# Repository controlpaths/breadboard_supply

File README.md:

# Breadboard Power supply

This tiny board generates all the voltages needed for your signal processing designs. 

This board features a bipolar power supply and a single voltage power supply for control.

The bipolar power supply is managed by a [TPS65131](https://www.ti.com/product/es-mx/TPS65131). A split-rail converter with a maximum output current of 750 mA. The outputs of this power supply is configured for -12 V and +13 volts. 

The board also has a 3v3 volts, 1 Amp output generated by an NCP1529.

All the power rails as well as the the enable input and the input voltage are connected through a 2.54mm right angle connector ready to be inserted into a breadboard. 

## Galery

## Get yours

This board is open-source, so if you want to get yours, you can use the [output_files](./kicad/output_files/) to manufacture your own in [JLCPCB](https://jlcpcb.com/?from=controlpath). You just need to compress the file of the [output_files](./kicad/output_files/) and upload it to [JLCPCB](https://jlcpcb.com/?from=controlpath)

Remember to change the Surface Finish to LeadFree HASL to make your board ROHS compliant.

Also, they can assemble your board using the [centroid](./kicad/output_files/ohe_power_supply_1-all-pos.csv) file and the [BOM](./kicad/output_files/bom.csv) file, which are also available in this repository. Doing this, in a few days you will receive in your home some of these boards.

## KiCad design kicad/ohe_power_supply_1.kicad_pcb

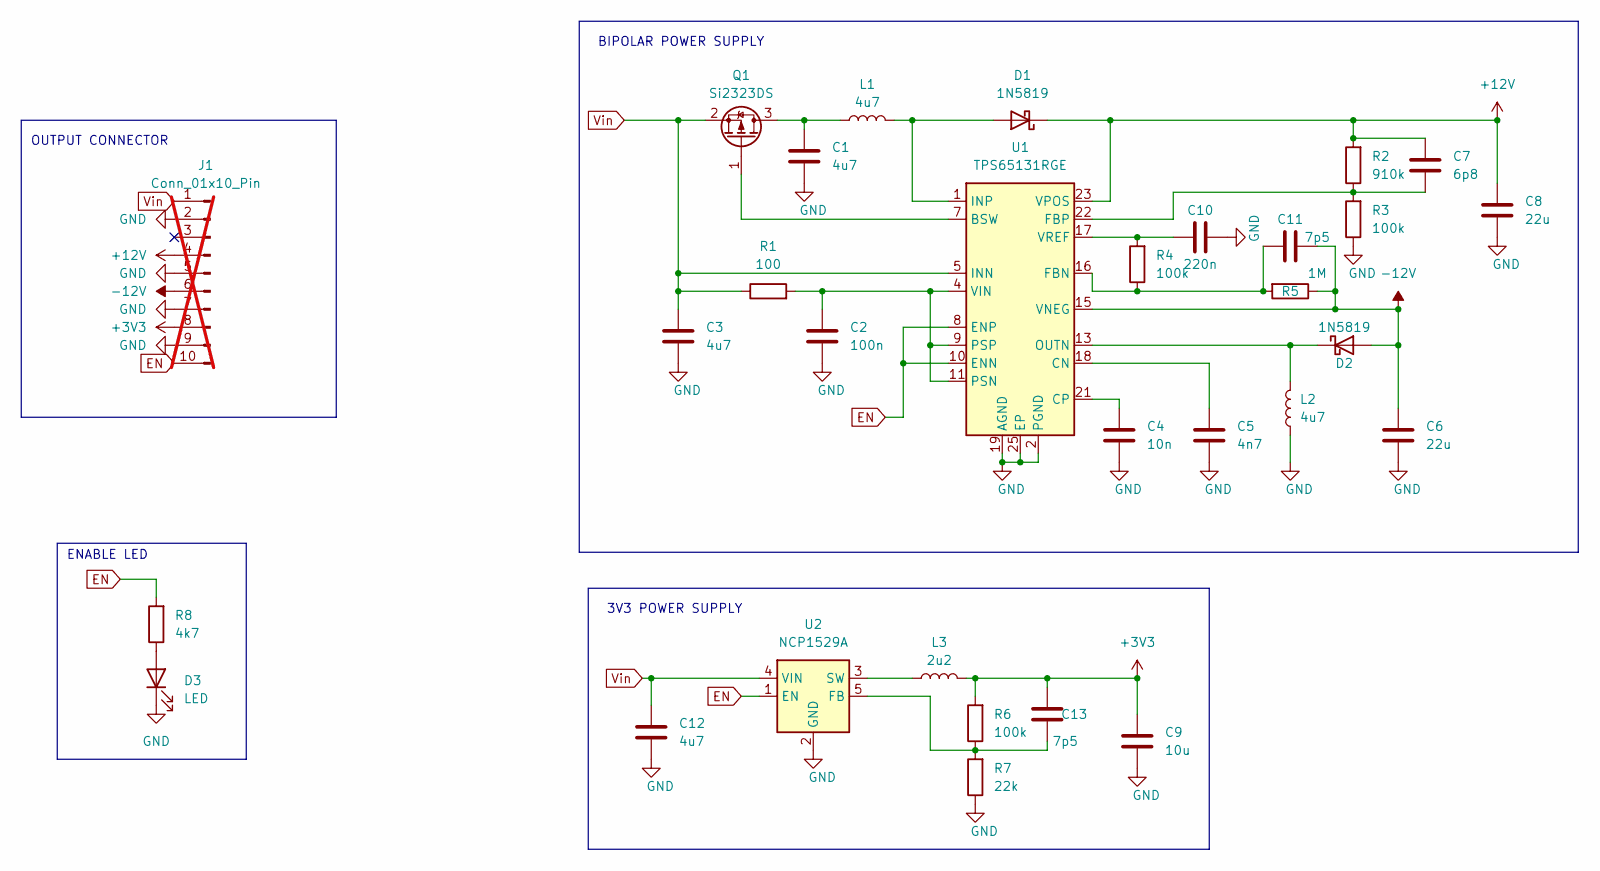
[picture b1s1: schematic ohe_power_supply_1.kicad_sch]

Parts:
C1, C3, C12: 4u7; C_0805_2012Metric
C2: 100n; C_0603_1608Metric
C4: 10n; C_0603_1608Metric
C5: 4n7; C_0603_1608Metric
C6, C8: 22u; C_0805_2012Metric
C7: 6p8; C_0603_1608Metric
C9: 10u; C_0805_2012Metric; JLCPCB Part # C307523
C10: 220n; C_0603_1608Metric
C11, C13: 7p5; C_0603_1608Metric
D1, D2: 1N5819; D_SOD-123; JLCPCB Part # C82544
D3: LED; LED_0603_1608Metric
J1: Conn_01x10_Pin; PinHeader_1x10_P2.54mm_Horizontal; not fitted
L1, L2: 4u7; L_Wurth_WE-LQSH-4020; JLCPCB Part # C2649331
L3: 2u2; L_1008_2520Metric; JLCPCB Part # C668447
Q1: Si2323DS; SOT-23; JLCPCB Part # C165449
R1: 100; R_0603_1608Metric
R2: 910k; R_0805_2012Metric; JLCPCB Part # C425483
R3, R4, R6: 100k; R_0603_1608Metric
R5: 1M; R_0603_1608Metric
R7: 22k; R_0603_1608Metric
R8: 4k7; R_0603_1608Metric
U1: TPS65131RGE; VQFN-24-1EP_4x4mm_P0.5mm_EP2.45x2.45mm_ThermalVias; JLCPCB Part # C87663
U2: NCP1529A; SOT-23-5

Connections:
+3V3: C9.1, C13.1, J1.8, L3.2, R6.2
+12V: C7.1, C8.1, D1.1 (K), J1.4, R2.2, U1.23 (VPOS)
-12V: C6.1, C11.2, D2.2 (A), J1.6, R5.1, U1.15 (VNEG)
EN: J1.10, R8.2, U1.8 (ENP), U1.10 (ENN), U2.1 (EN)
GND: C1.2, C2.2, C3.2, C4.2, C5.2, C6.2, C8.2, C9.2, C10.2, C12.2, D3.1 (K), J1.2, J1.5, J1.7, J1.9, L2.1, R3.1, R7.1, U1.2 (PGND), U1.3 (PGND), U1.19 (AGND), U1.25 (EP), U2.2 (GND)
unnamed: D1.2 (A), L1.2, U1.1 (INP), U1.24 (INP)
unnamed: D2.1 (K), L2.2, U1.13 (OUTN), U1.14 (OUTN)
unnamed: D3.2 (A), R8.1
unnamed: C1.1, L1.1, Q1.3 (D)
unnamed: Q1.1 (G), U1.7 (BSW)
unnamed: C5.1, U1.18 (CN)
unnamed: C4.1, U1.21 (CP)
unnamed: C11.1, R4.1, R5.2, U1.16 (FBN)
unnamed: C7.2, R2.1, R3.2, U1.22 (FBP)
unnamed: C2.1, R1.2, U1.4 (VIN), U1.9 (PSP), U1.11 (PSN)
unnamed: C10.1, R4.2, U1.17 (VREF)
unnamed: C13.2, R6.1, R7.2, U2.5 (FB)
unnamed: L3.1, U2.3 (SW)
Vin: C3.1, C12.1, J1.1, Q1.2 (S), R1.1, U1.5 (INN), U1.6 (INN), U2.4 (VIN)

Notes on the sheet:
3V3 POWER SUPPLY
ENABLE LED
OUTPUT CONNECTOR
BIPOLAR POWER SUPPLY

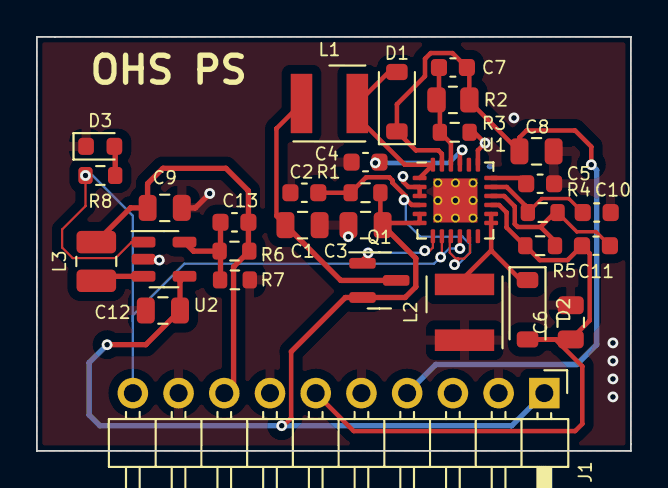
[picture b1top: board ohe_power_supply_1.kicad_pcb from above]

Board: 2 copper layers, 33.0 x 23.0 mm, 31 parts (0 on the bottom side), 19 nets.

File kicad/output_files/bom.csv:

"#","Reference","Qty","Value","Footprint","DNP","JLCPCB Part #"
"1","C1, C3, C12","3","4u7","Capacitor_SMD:C_0805_2012Metric","",""
"2","C2","1","100n","Capacitor_SMD:C_0603_1608Metric","",""
"3","C4","1","10n","Capacitor_SMD:C_0603_1608Metric","",""
"4","C5","1","4n7","Capacitor_SMD:C_0603_1608Metric","",""
"5","C6, C8","2","22u","Capacitor_SMD:C_0805_2012Metric","",""
"6","C7","1","6p8","Capacitor_SMD:C_0603_1608Metric","",""
"7","C9","1","10u","Capacitor_SMD:C_0805_2012Metric","",""
"8","C10","1","220n","Capacitor_SMD:C_0603_1608Metric","",""
"9","C11, C13","2","7p5","Capacitor_SMD:C_0603_1608Metric","",""
"10","D1, D2","2","1N5819","Diode_SMD:D_SOD-123","","C82544"
"11","D3","1","LED","LED_SMD:LED_0603_1608Metric","",""
"12","J1","1","Conn_01x10_Pin","Connector_PinHeader_2.54mm:PinHeader_1x10_P2.54mm_Horizontal","DNP",""
"13","L1, L2","2","4u7","Inductor_SMD_Wurth:L_Wurth_WE-LQSH-4020","","C2649331"
"14","L3","1","2u2","Inductor_SMD:L_1008_2520Metric","","C668447"
"15","Q1","1","Si2323DS","Package_TO_SOT_SMD:SOT-23","","C165449"
"16","R1","1","100","Resistor_SMD:R_0603_1608Metric","",""
"17","R2","1","910k","Resistor_SMD:R_0805_2012Metric","","C425483"
"18","R3, R4, R6","3","100k","Resistor_SMD:R_0603_1608Metric","",""
"19","R5","1","1M","Resistor_SMD:R_0603_1608Metric","",""
"20","R7","1","22k","Resistor_SMD:R_0603_1608Metric","",""
"21","R8","1","4k7","Resistor_SMD:R_0603_1608Metric","",""
"22","U1","1","TPS65131RGE","Package_DFN_QFN:VQFN-24-1EP_4x4mm_P0.5mm_EP2.45x2.45mm_ThermalVias","","C87663"
"23","U2","1","NCP1529A","Package_TO_SOT_SMD:SOT-23-5","",""

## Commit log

2024-01-08 project uploaded
